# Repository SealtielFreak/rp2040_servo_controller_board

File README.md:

# Servo Controller Board
Servo Controller Board for Raspberry Pi Pico

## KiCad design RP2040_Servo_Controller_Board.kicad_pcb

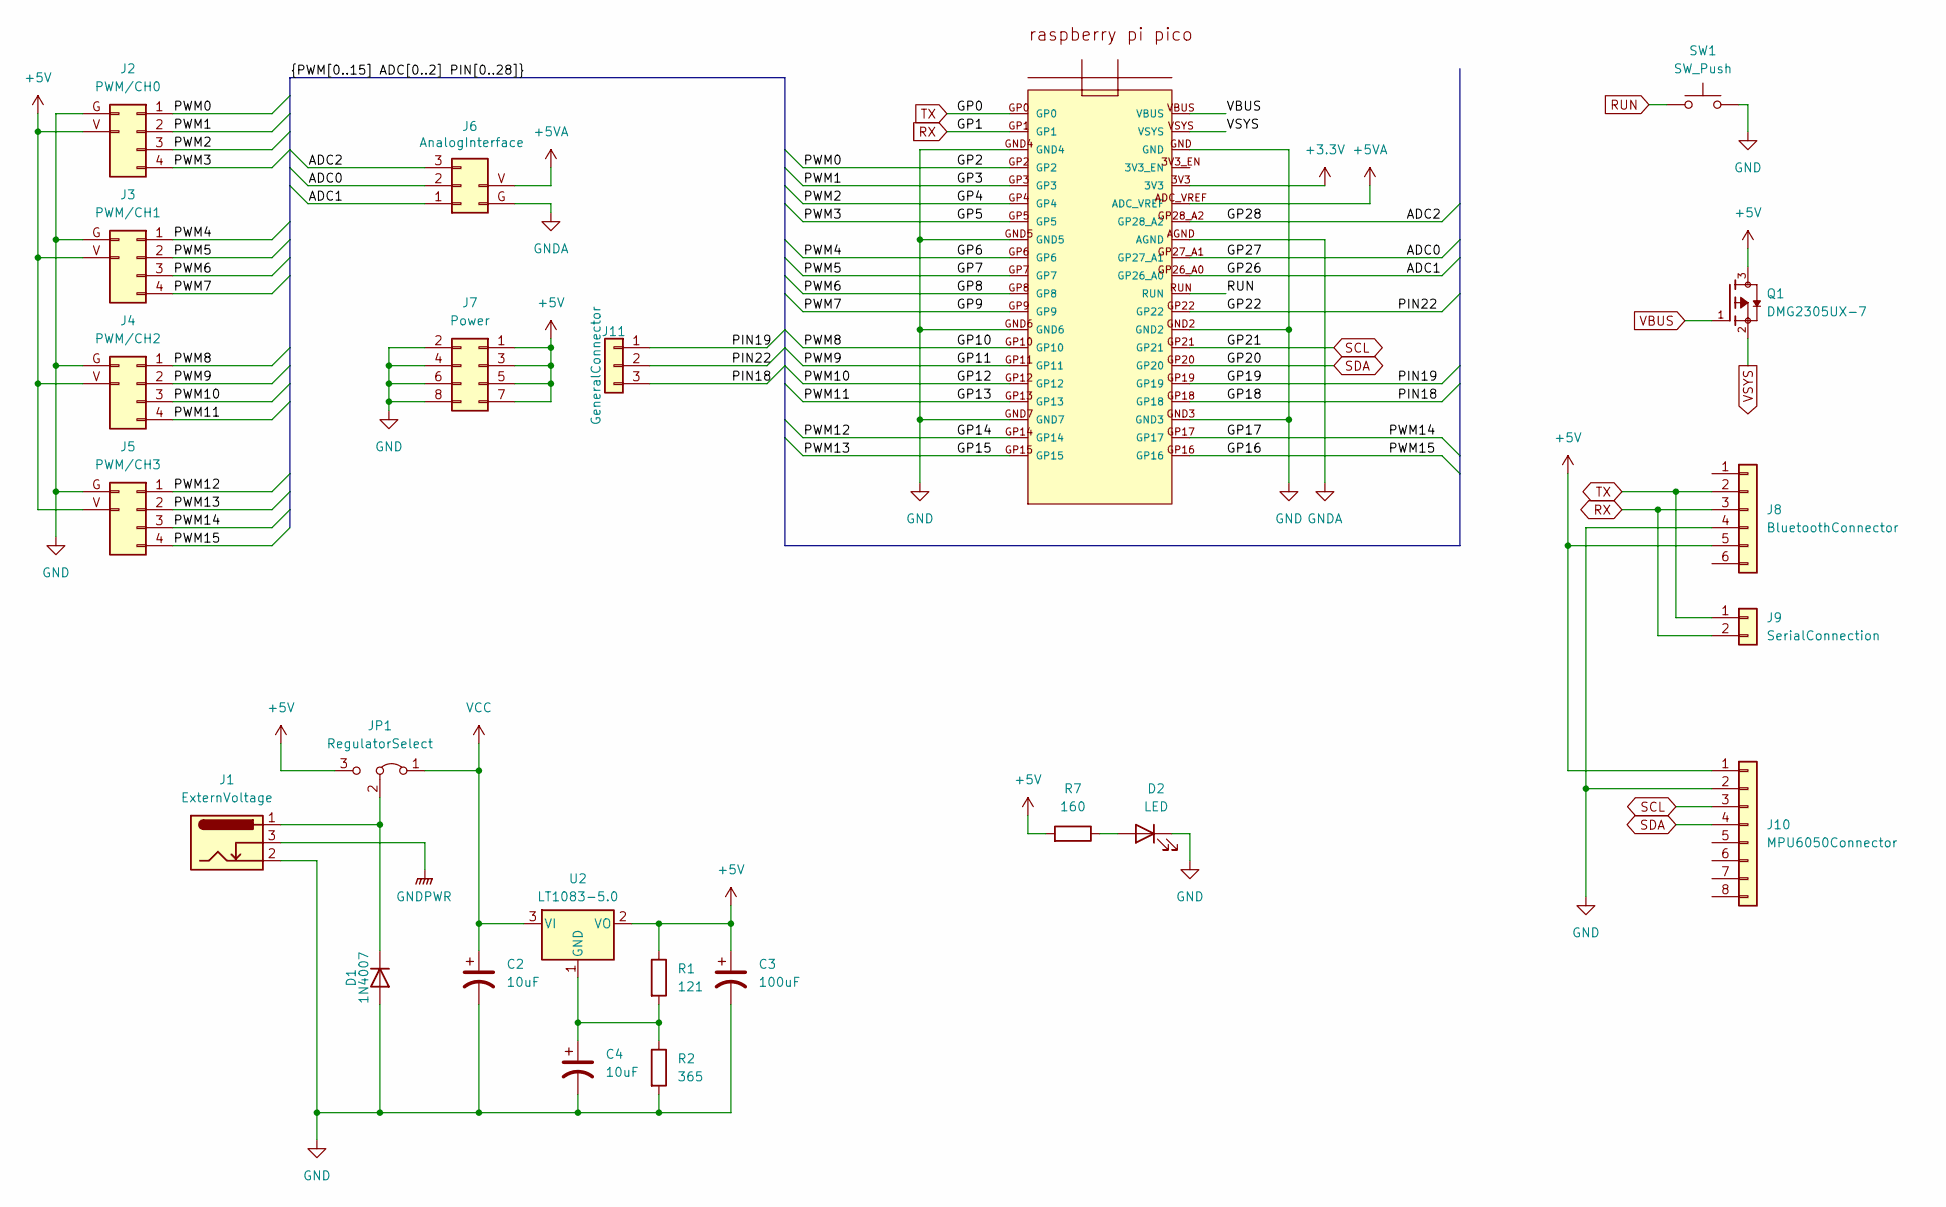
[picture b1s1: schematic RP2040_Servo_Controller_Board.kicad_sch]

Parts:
C2, C4: 10uF; CP_Radial_D4.0mm_P2.00mm
C3: 100uF; CP_Radial_D4.0mm_P2.00mm
D1: 1N4007; D_A-405_P7.62mm_Horizontal
D2: LED; LED_D3.0mm
J1: ExternVoltage; BarrelJack_Horizontal
J2: PWM/CH0; PinHeader_3x04_P2.54mm
J3: PWM/CH1; PinHeader_3x04_P2.54mm
J4: PWM/CH2; PinHeader_3x04_P2.54mm
J5: PWM/CH3; PinHeader_3x04_P2.54mm
J6: AnalogInterface; PinHeader_3x03_P2.54mm
J7: Power; PinHeader_2x04_P2.54mm_Vertical
J8: BluetoothConnector; PinSocket_1x06_P2.54mm_Vertical
J9: SerialConnection; PinSocket_1x02_P2.54mm_Vertical
J10: MPU6050Connector; PinSocket_1x08_P2.54mm_Vertical
J11: GeneralConnector; PinSocket_1x03_P2.54mm_Vertical
JP1: RegulatorSelect; PinHeader_1x03_P2.54mm_Vertical
Q1: DMG2305UX-7; SOT91P240X110-3N_DMG2305UX-7; PARTREV 09/2018
R1: 121; R_Axial_DIN0204_L3.6mm_D1.6mm_P5.08mm_Horizontal
R2: 365; R_Axial_DIN0204_L3.6mm_D1.6mm_P5.08mm_Horizontal
R7: 160; R_Axial_DIN0204_L3.6mm_D1.6mm_P5.08mm_Horizontal
SW1: SW_Push; SW_PUSH_6mm
U1: RP2040; RP2040_Module_THL
U2: LT1083-5.0; TO-220F-3_Vertical

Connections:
+3.3V: U1.3V3
+5V: C3.1, J2.V, J3.V, J4.V, J5.V, J7.1, J7.3, J7.5, J7.7, J8.5, J10.1, JP1.3 (B), Q1.3, R1.1, R7.2, U2.2 (VO)
+5VA: J6.V, U1.ADC_VREF
/ADC0: J6.2, U1.GP27_A1
/ADC1: J6.1, U1.GP26_A0
/ADC2: J6.3, U1.GP28_A2
/PIN18: J11.3, U1.GP18
/PIN19: J11.1, U1.GP19
/PIN22: J11.2, U1.GP22
/PWM0: J2.1, U1.GP2
/PWM1: J2.2, U1.GP3
/PWM2: J2.3, U1.GP4
/PWM3: J2.4, U1.GP5
/PWM4: J3.1, U1.GP6
/PWM5: J3.2, U1.GP7
/PWM6: J3.3, U1.GP8
/PWM7: J3.4, U1.GP9
/PWM8: J4.1, U1.GP10
/PWM9: J4.2, U1.GP11
/PWM10: J4.3, U1.GP12
/PWM11: J4.4, U1.GP13
/PWM12: J5.1, U1.GP14
/PWM13: J5.2, U1.GP15
/PWM14: J5.3, U1.GP17
/PWM15: J5.4, U1.GP16
GND: C2.2, C3.2, C4.2, D1.2 (A), D2.1 (K), J1.2, J2.G, J3.G, J4.G, J5.G, J7.2, J7.4, J7.6, J7.8, J8.4, J10.2, R2.2, SW1.2, U1.GND, U1.GND2, U1.GND3, U1.GND4, U1.GND5, U1.GND6, U1.GND7
GNDA: J6.G, U1.AGND
GNDPWR: J1.3
unnamed: D1.1 (K), J1.1, JP1.2 (C)
unnamed: D2.2 (A), R7.1
unnamed: C4.1, R1.2, R2.1, U2.1 (GND)
RUN: SW1.1, U1.RUN
RX: J8.3, J9.2, U1.GP1
SCL: J10.3, U1.GP21
SDA: J10.4, U1.GP20
TX: J8.2, J9.1, U1.GP0
VBUS: Q1.1, U1.VBUS
VCC: C2.1, JP1.1 (A), U2.3 (VI)
VSYS: Q1.2, U1.VSYS

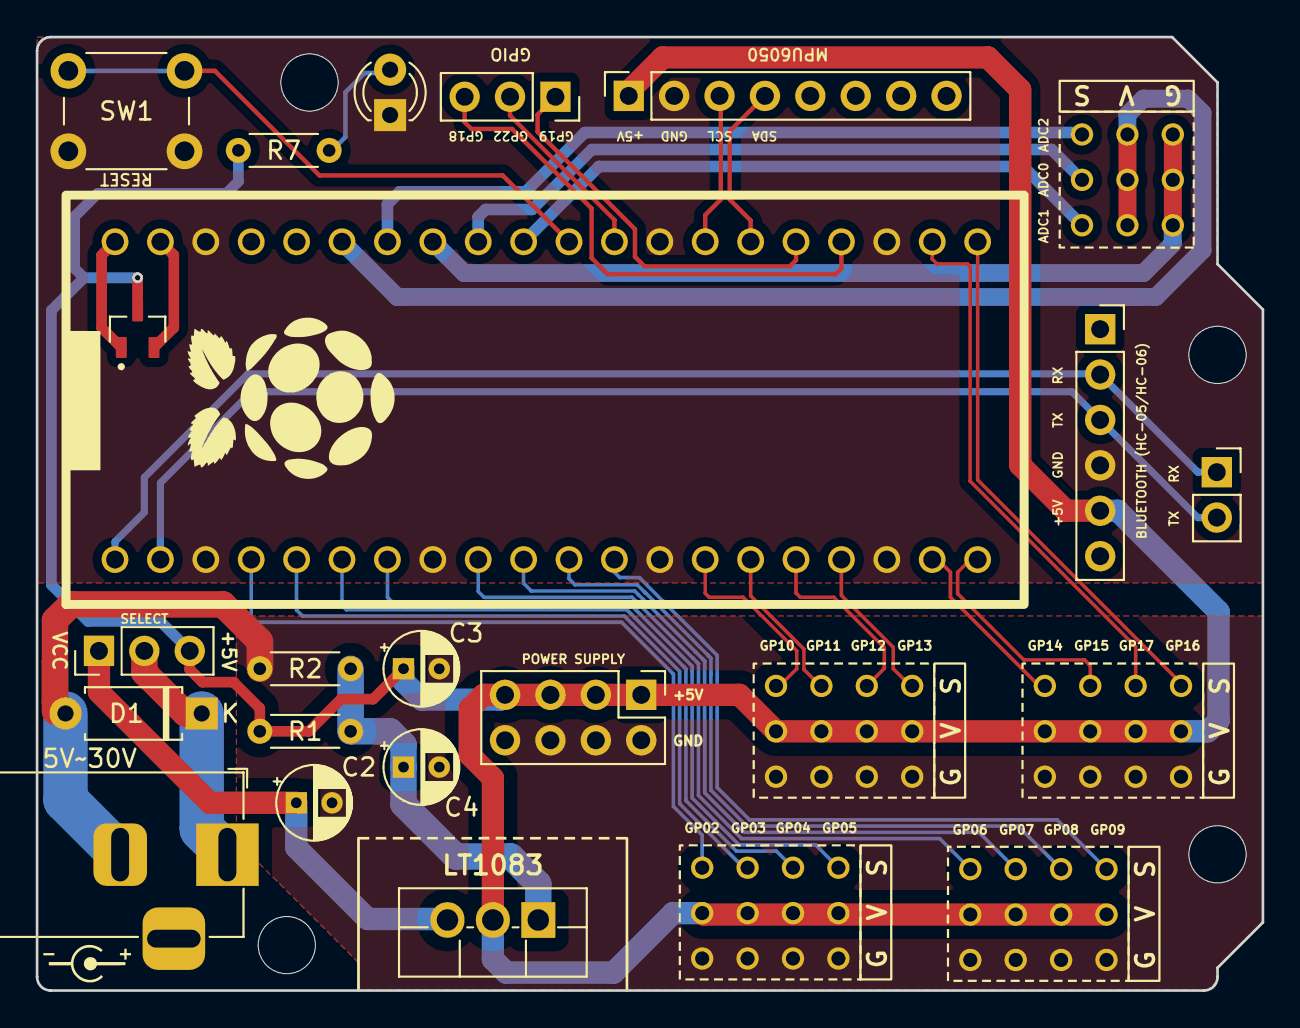
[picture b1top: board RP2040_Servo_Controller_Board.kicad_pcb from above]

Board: 2 copper layers, 68.6 x 53.3 mm, 30 parts (1 on the bottom side), 37 nets.

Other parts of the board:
G1, G3: LOGO
MH1, MH2, MH3, MH4: MountingHole_3.2mm

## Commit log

2024-05-09 Change LICENSE
